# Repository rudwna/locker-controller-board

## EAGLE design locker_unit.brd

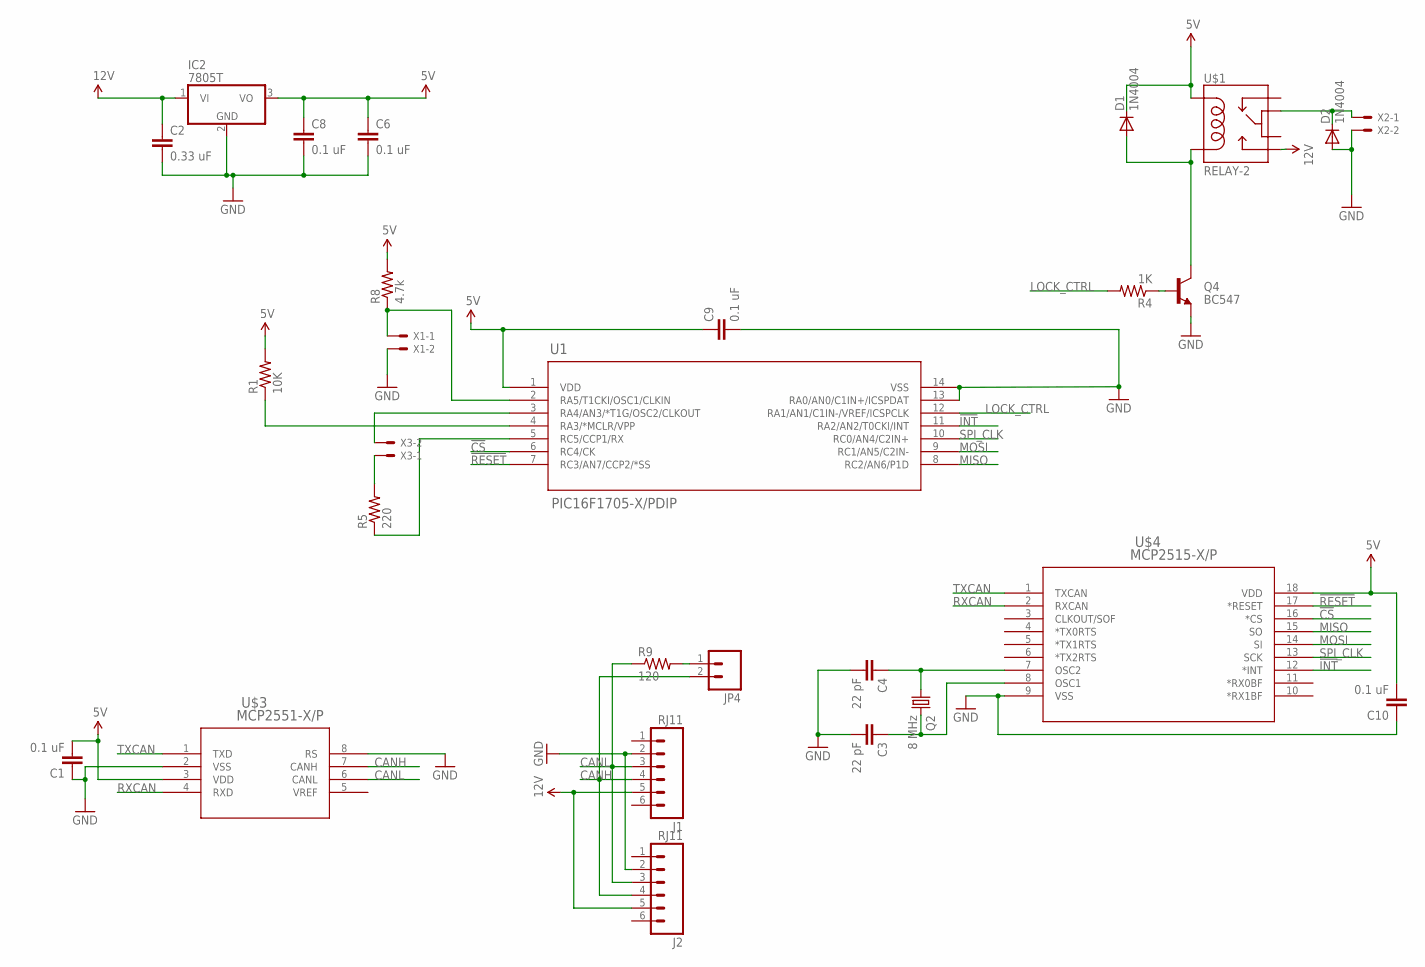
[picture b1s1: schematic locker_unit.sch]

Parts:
C1, C6, C8, C9, C10: 0.1 uF; C050-030X075
C2: 0.33 uF; C050-030X075
C3, C4: 22 pF; C025-025X050
D1, D2: 1N4004; DO41-10
IC2: 7805T; TO220H
J1, J2: RJ11; RJ11-6
JP4: M02PTH; 1X02
Q2: 8 MHz; HC49US
Q4: BC547; TO-92-AMMO
R1: 10K; AXIAL-0.3
R4: 1K; AXIAL-0.3
R5: 220; AXIAL-0.3
R8: 4.7k; AXIAL-0.3
R9: 120; AXIAL-0.3
U1: PIC16F1705-X/PDIP; PDIP14_300MC
U$1: RELAY-2; RELAY-SY
U$3: MCP2551-X/P; PDIP8_300MC
U$4: MCP2515-X/P; PDIP18_300MC
X1, X2, X3: KK-156-2

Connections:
5V: C1.2, C6.1, C8.1, C9.1, C10.2, D1.C, IC2.3 (VO), R1.P$2 (2), R8.P$2 (2), U1.1 (VDD), U$1.2, U$3.3 (VDD), U$4.18 (VDD)
12V: C2.1, IC2.1 (VI), J1.5, J2.5, U$1.10
!CS: U1.6 (RC4/CK), U$4.16 (*CS)
!INT: U1.11 (RA2/AN2/T0CKI/INT), U$4.12 (*INT)
!RESET: U1.7 (RC3/AN7/CCP2/*SS), U$4.17 (*RESET)
CANH: J1.4, J2.4, JP4.2, U$3.7 (CANH)
CANL: J1.3, J2.3, R9.P$1 (1), U$3.6 (CANL)
GND: C1.1, C2.2, C3.2, C4.2, C6.2, C8.2, C9.2, C10.1, D2.A, IC2.2 (GND), J1.2, J2.2, Q4.3 (E), U1.13 (RA0/AN0/C1IN+/ICSPDAT), U1.14 (VSS), U$3.2 (VSS), U$3.8 (RS), U$4.9 (VSS), X1.2, X2.2
LOCK_CTRL: R4.P$2 (2), U1.12 (RA1/AN1/C1IN-/VREF/ICSPCLK)
MISO: U1.8 (RC2/AN6/P1D), U$4.15 (SO)
MOSI: U1.9 (RC1/AN5/C2IN-), U$4.14 (SI)
unnamed: D2.C, U$1.5, X2.1
unnamed: R5.P$1 (1), U1.5 (RC5/CCP1/RX)
unnamed: D1.A, Q4.1 (C), U$1.9
unnamed: Q4.2 (B), R4.P$1 (1)
unnamed: R5.P$2 (2), X3.1
unnamed: R1.P$1 (1), U1.4 (RA3/*MCLR/VPP)
unnamed: C3.1, Q2.2, U$4.8 (OSC1)
unnamed: C4.1, Q2.1, U$4.7 (OSC2)
unnamed: U1.3 (RA4/AN3/*T1G/OSC2/CLKOUT), X3.2
unnamed: R8.P$1 (1), U1.2 (RA5/T1CKI/OSC1/CLKIN), X1.1
unnamed: JP4.1, R9.P$2 (2)
RXCAN: U$3.4 (RXD), U$4.2 (RXCAN)
SPI_CLK: U1.10 (RC0/AN4/C2IN+), U$4.13 (SCK)
TXCAN: U$3.1 (TXD), U$4.1 (TXCAN)

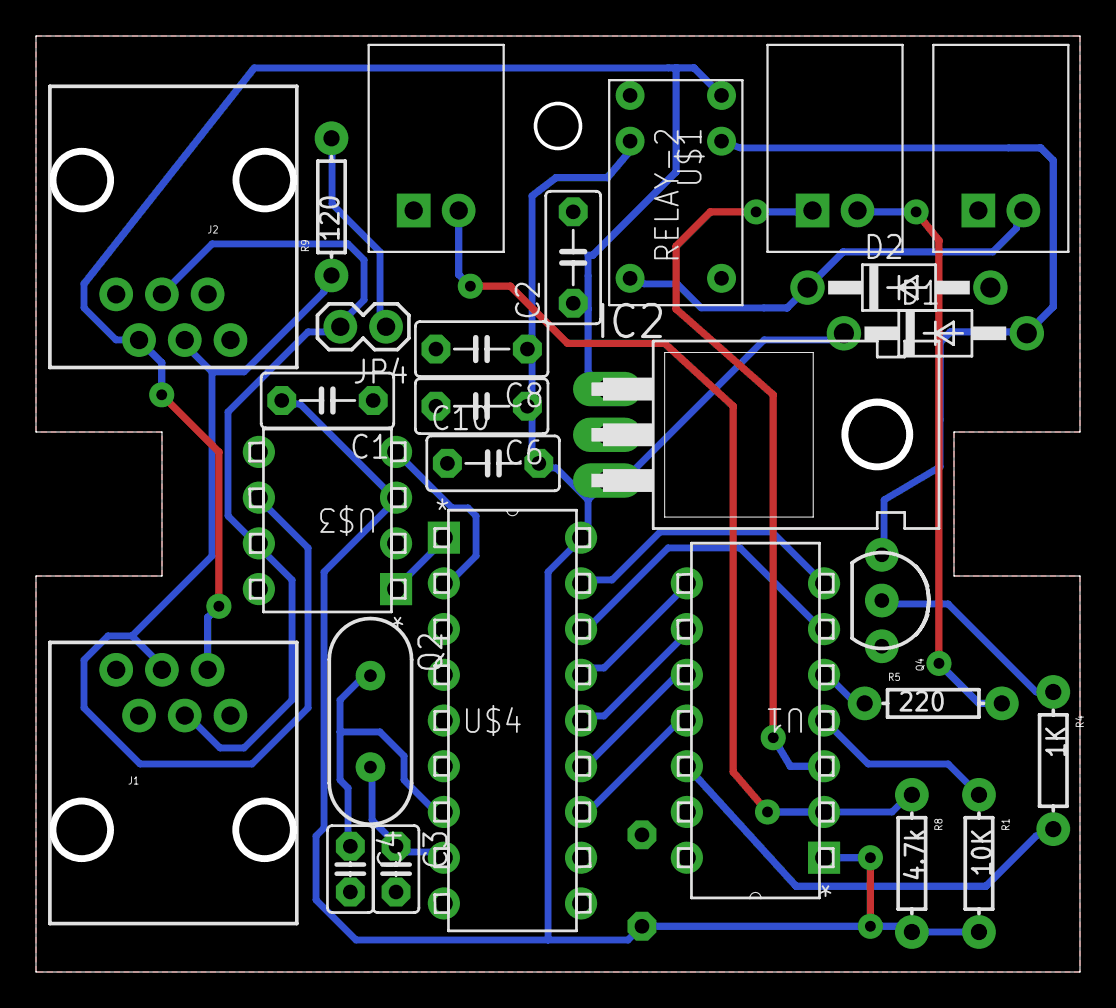
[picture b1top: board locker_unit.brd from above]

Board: 2 copper layers, 58.0 x 52.0 mm, 28 parts (1 on the bottom side), 25 nets.

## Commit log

2015-06-20 Add board file
2015-06-28 Edit whole layout, add external LED header. Should be the final version.
2015-07-02 Eagle edit?

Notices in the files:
parts and their libraries:
SparkFun-Connectors: Licensing: Creative Commons ShareAlike 4.0 International - https://creativecommons.org/licenses/by-sa/4.0
